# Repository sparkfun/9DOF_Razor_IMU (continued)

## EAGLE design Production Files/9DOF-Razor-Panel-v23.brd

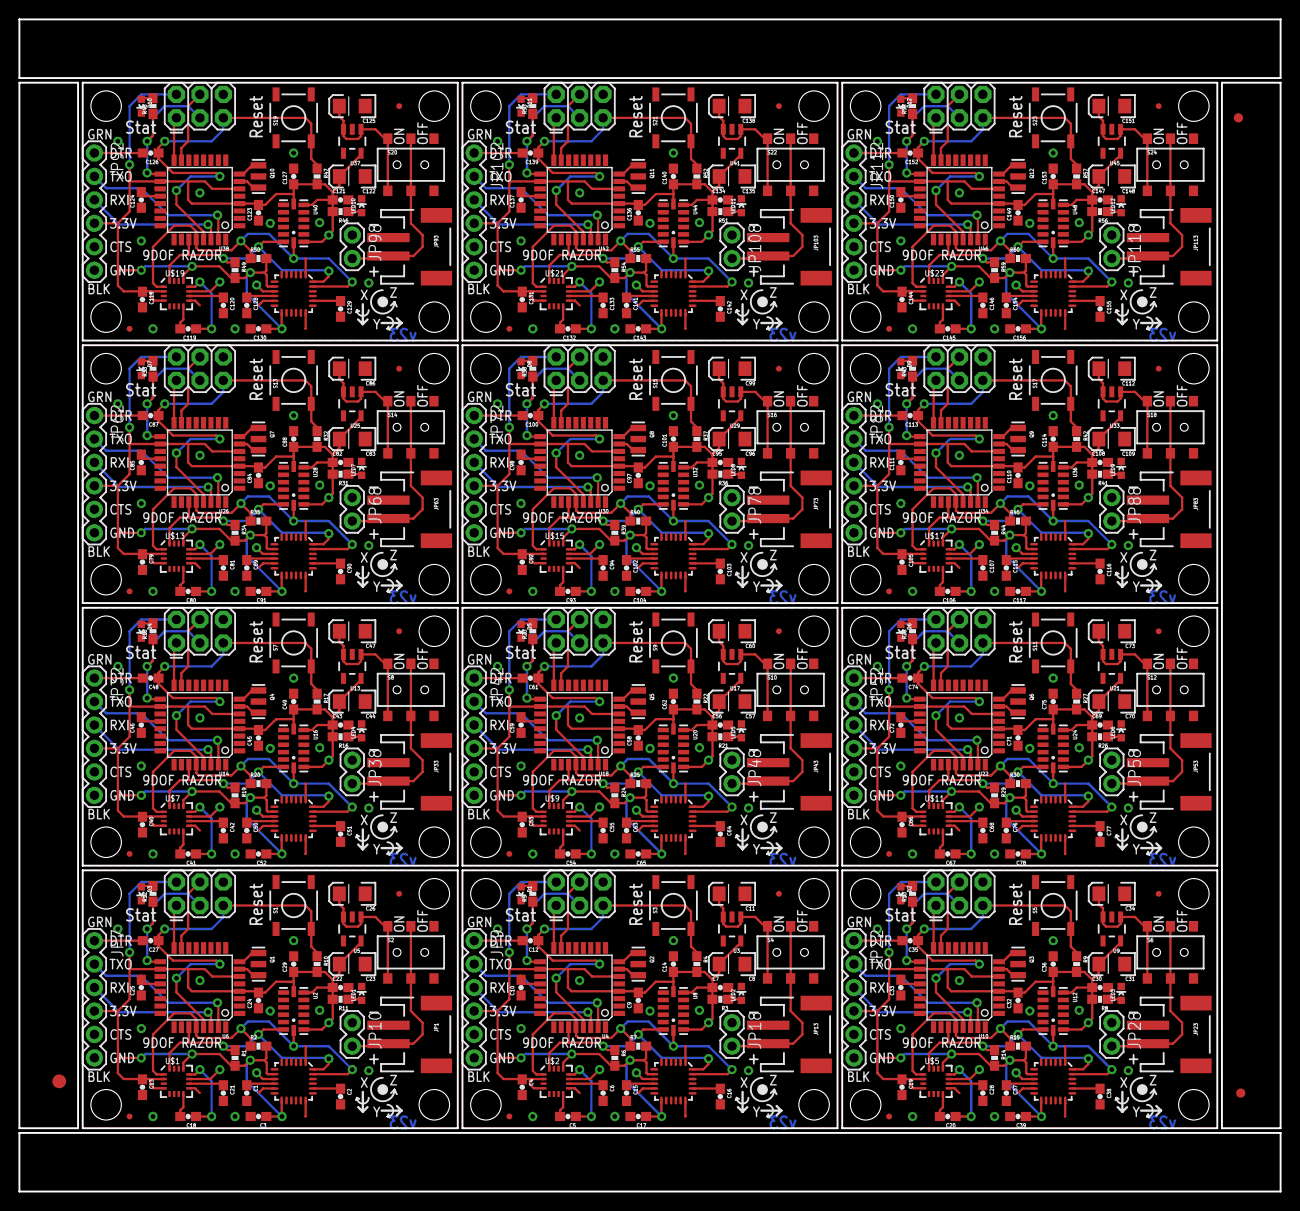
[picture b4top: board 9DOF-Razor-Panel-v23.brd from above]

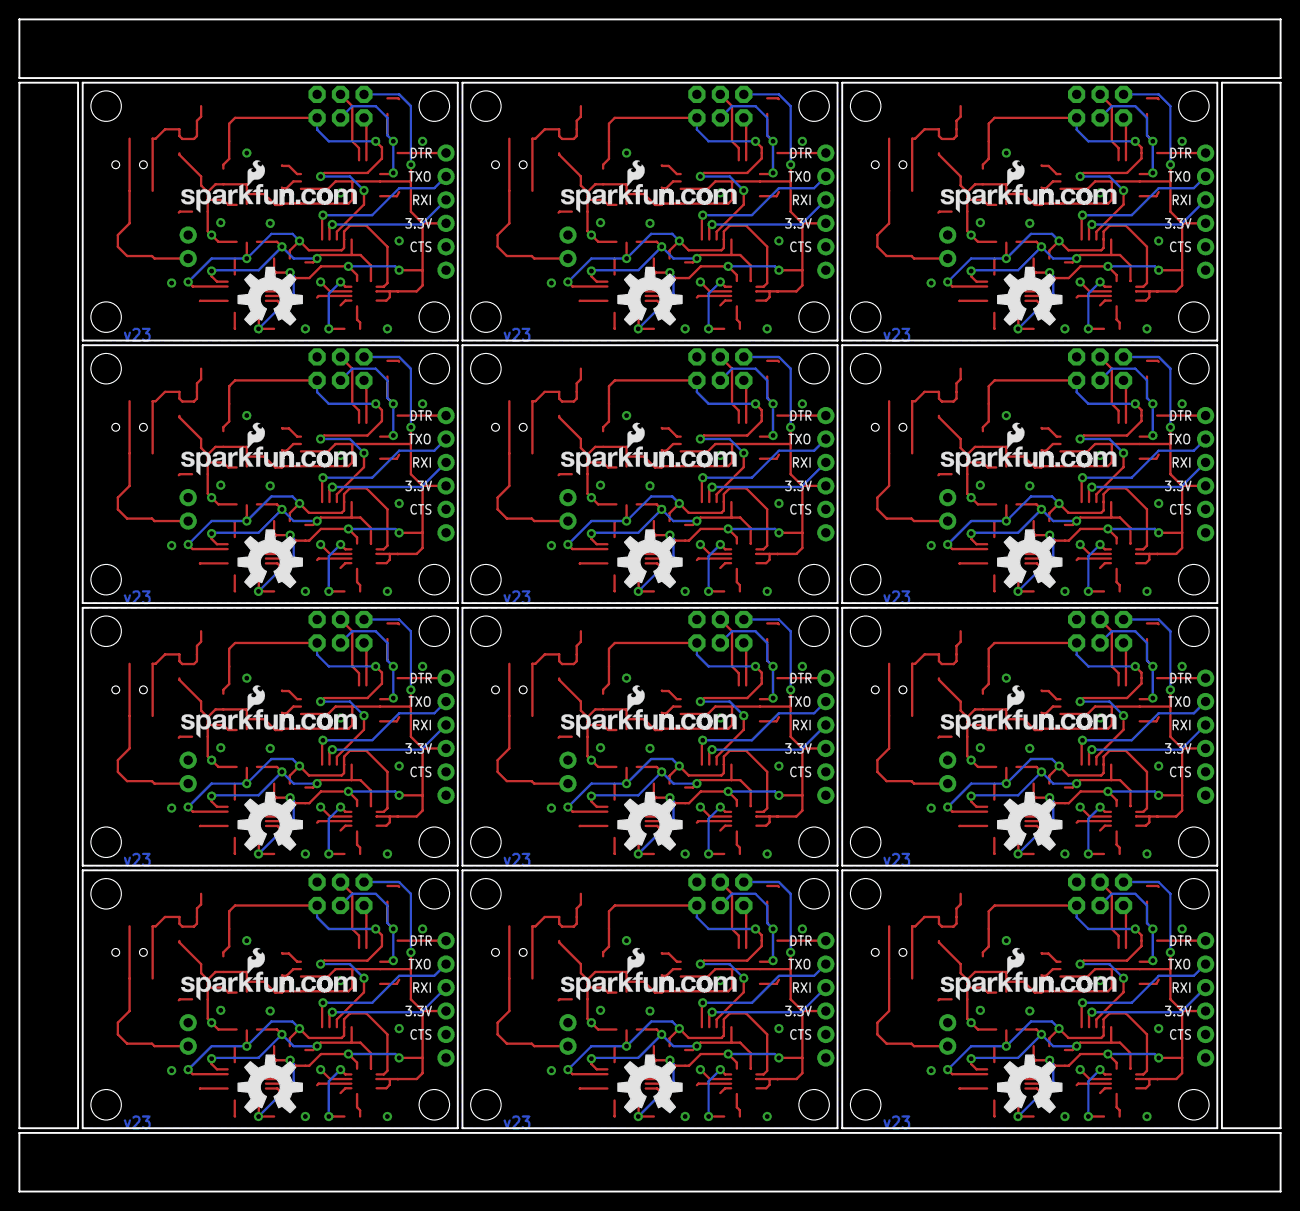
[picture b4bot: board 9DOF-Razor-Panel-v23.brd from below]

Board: 2 copper layers, 136.7 x 127.0 mm, 483 parts (24 on the bottom side), 276 nets.

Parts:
C1, C4, C7, C9, C10, C12, C13, C14, C15, C19, C22, C24, C25, C27, C29, C30, C32, C33, C35, C36, C37, C40, C43, C45, C46, C48, C49, C50, C53, C56, C58, C59, C61, C62, C63, C66, C69, C71, C72, C74, C75, C76, C79, C82, C84, C85, C87, C88, C89, C92, C95, C97, C98, C100, C101, C102, C105, C108, C110, C111, C113, C114, C115, C118, C121, C123, C124, C126, C127, C128, C131, C134, C136, C137, C139, C140, C141, C144, C147, C149, C150, C152, C153, C154: 0.1uF; 0603-CAP
C2, C16, C38, C51, C64, C77, C90, C103, C116, C129, C142, C155: 2.2nF; 0603-CAP
C3, C17, C39, C52, C65, C78, C91, C104, C117, C130, C143, C156: 10nF; 0603-CAP
C5, C18, C20, C41, C54, C67, C80, C93, C106, C119, C132, C145: 0.22uF; 0603-CAP
C6, C21, C28, C42, C55, C68, C81, C94, C107, C120, C133, C146: 4.7uF; 0603-CAP
C8, C11, C23, C26, C31, C34, C44, C47, C57, C60, C70, C73, C83, C86, C96, C99, C109, C112, C122, C125, C135, C138, C148, C151: 10uF; EIA3216
D1, D2, D3, D4, D5, D6, D7, D8, D9, D10, D11, D12: Green; LED-0603
E$1: FIDUCIAL-1.5X3
E$4, E$5: FIDUCIAL-1X2
J1, J2, J3, J4, J5, J6, J7, J8, J9, J10, J11, J12: AVR_SPI_PRG_6PTH; 2X3
JP1, JP13, JP23, JP33, JP43, JP53, JP63, JP73, JP83, JP93, JP103, JP113: JST_Horizontal; JST-2-SMD
JP2, JP4, JP5, JP6, JP14, JP15, JP16, JP17, JP24, JP25, JP26, JP27, JP34, JP35, JP36, JP37, JP44, JP45, JP46, JP47, JP54, JP55, JP56, JP57, JP64, JP65, JP66, JP67, JP74, JP75, JP76, JP77, JP84, JP85, JP86, JP87, JP94, JP95, JP96, JP97, JP104, JP105, JP106, JP107, JP114, JP115, JP116, JP117: STAND-OFF
JP3, JP8, JP21, JP31, JP41, JP51, JP61, JP71, JP81, JP91, JP101, JP111: LOGO-SFENEW; SFE-NEW-WEBLOGO
JP7, JP9, JP22, JP32, JP42, JP52, JP62, JP72, JP82, JP92, JP102, JP112: FTDI Basic; 1X06
JP10, JP18, JP28, JP38, JP48, JP58, JP68, JP78, JP88, JP98, JP108, JP118: JST_Horizontal; 1X02
JP11, JP12, JP19, JP20, JP29, JP30, JP39, JP40, JP49, JP50, JP59, JP60, JP69, JP70, JP79, JP80, JP89, JP90, JP99, JP100, JP109, JP110, JP119, JP120: FIDUCIAL1X2.5; FIDUCIAL-1X2.5
LED1, LED2, LED3, LED4, LED5, LED6, LED7, LED8, LED9, LED10, LED11, LED12: Red; LED-0603
Q1, Q2, Q3, Q4, Q5, Q6, Q7, Q8, Q9, Q10, Q11, Q12: 8MHz; RESONATOR-SMD
R1, R6, R14, R19, R24, R29, R34, R39, R44, R49, R54, R59: 4.7k; 0603-RES
R2, R7, R15, R20, R25, R30, R35, R40, R45, R50, R55, R60: 4.7K; 0603-RES
R3, R4, R8, R9, R10, R11, R16, R17, R21, R22, R26, R27, R31, R32, R36, R37, R41, R42, R46, R47, R51, R52, R56, R57: 10K; 0603-RES
R5, R12, R13, R18, R23, R28, R33, R38, R43, R48, R53, R58: 330; 0603-RES
S1, S3, S5, S7, S9, S11, S13, S15, S17, S19, S21, S23: Reset; TACTILE_SWITCH_SMD
S2, S4, S6, S8, S10, S12, S14, S16, S18, S20, S22, S24: Power; AYZ0202
U1, U7, U11, U15, U19, U23, U27, U31, U35, U39, U43, U47: ITG-32001:1; QFN-24_ITG3200_1:1
U2, U8, U12, U16, U20, U24, U28, U32, U36, U40, U44, U48: ADXL3451:1; LGA14
U3, U5, U9, U13, U17, U21, U25, U29, U33, U37, U41, U45: 3.3V; SOT23-5
U4, U6, U10, U14, U18, U22, U26, U30, U34, U38, U42, U46: ATMEGA328; TQFP32-08
U$1, U$2, U$5, U$7, U$9, U$11, U$13, U$15, U$17, U$19, U$21, U$23: HMC5883LSMD; 16LPCC
U$3, U$4, U$6, U$8, U$10, U$12, U$14, U$16, U$18, U$20, U$22, U$24: OSHW-LOGOL; OSHW-LOGO-L

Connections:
3.3V: C3.1, C13.1, C22.1, C23.A, C24.2, C29.1, J1.2, JP7.4, R1.2, R2.2, R10.2, R11.2, U1.8, U1.13, U2.1, U2.6, U2.7, U5.5, U6.4, U6.6, U6.18, U$1.2, U$1.4, U$1.13
3.3V1: C4.1, C7.1, C8.A, C9.2, C14.1, C17.1, J2.2, JP9.4, R3.2, R4.2, R6.2, R7.2, U3.5, U4.4, U4.6, U4.18, U7.8, U7.13, U8.1, U8.6, U8.7, U$2.2, U$2.4, U$2.13
3.3V2: C19.1, C30.1, C31.A, C32.2, C36.1, C39.1, J3.2, JP22.4, R8.2, R9.2, R14.2, R15.2, U9.5, U10.4, U10.6, U10.18, U11.8, U11.13, U12.1, U12.6, U12.7, U$5.2, U$5.4, U$5.13
3.3V3: C40.1, C43.1, C44.A, C45.2, C49.1, C52.1, J4.2, JP32.4, R16.2, R17.2, R19.2, R20.2, U13.5, U14.4, U14.6, U14.18, U15.8, U15.13, U16.1, U16.6, U16.7, U$7.2, U$7.4, U$7.13
3.3V4: C53.1, C56.1, C57.A, C58.2, C62.1, C65.1, J5.2, JP42.4, R21.2, R22.2, R24.2, R25.2, U17.5, U18.4, U18.6, U18.18, U19.8, U19.13, U20.1, U20.6, U20.7, U$9.2, U$9.4, U$9.13
3.3V5: C66.1, C69.1, C70.A, C71.2, C75.1, C78.1, J6.2, JP52.4, R26.2, R27.2, R29.2, R30.2, U21.5, U22.4, U22.6, U22.18, U23.8, U23.13, U24.1, U24.6, U24.7, U$11.2, U$11.4, U$11.13
3.3V6: C79.1, C82.1, C83.A, C84.2, C88.1, C91.1, J7.2, JP62.4, R31.2, R32.2, R34.2, R35.2, U25.5, U26.4, U26.6, U26.18, U27.8, U27.13, U28.1, U28.6, U28.7, U$13.2, U$13.4, U$13.13
3.3V7: C92.1, C95.1, C96.A, C97.2, C101.1, C104.1, J8.2, JP72.4, R36.2, R37.2, R39.2, R40.2, U29.5, U30.4, U30.6, U30.18, U31.8, U31.13, U32.1, U32.6, U32.7, U$15.2, U$15.4, U$15.13
3.3V8: C105.1, C108.1, C109.A, C110.2, C114.1, C117.1, J9.2, JP82.4, R41.2, R42.2, R44.2, R45.2, U33.5, U34.4, U34.6, U34.18, U35.8, U35.13, U36.1, U36.6, U36.7, U$17.2, U$17.4, U$17.13
3.3V9: C118.1, C121.1, C122.A, C123.2, C127.1, C130.1, J10.2, JP92.4, R46.2, R47.2, R49.2, R50.2, U37.5, U38.4, U38.6, U38.18, U39.8, U39.13, U40.1, U40.6, U40.7, U$19.2, U$19.4, U$19.13
3.3V10: C131.1, C134.1, C135.A, C136.2, C140.1, C143.1, J11.2, JP102.4, R51.2, R52.2, R54.2, R55.2, U41.5, U42.4, U42.6, U42.18, U43.8, U43.13, U44.1, U44.6, U44.7, U$21.2, U$21.4, U$21.13
3.3V11: C144.1, C147.1, C148.A, C149.2, C153.1, C156.1, J12.2, JP112.4, R56.2, R57.2, R59.2, R60.2, U45.5, U46.4, U46.6, U46.18, U47.8, U47.13, U48.1, U48.6, U48.7, U$23.2, U$23.4, U$23.13
AREF: C25.2, U6.20
AREF1: C10.2, U4.20
AREF2: C33.2, U10.20
AREF3: C46.2, U14.20
AREF4: C59.2, U18.20
AREF5: C72.2, U22.20
AREF6: C85.2, U26.20
AREF7: C98.2, U30.20
AREF8: C111.2, U34.20
AREF9: C124.2, U38.20
AREF10: C137.2, U42.20
AREF11: C150.2, U46.20
DTR: C27.2, JP7.1
DTR1: C12.2, JP9.1
DTR2: C35.2, JP22.1
DTR3: C48.2, JP32.1
DTR4: C61.2, JP42.1
DTR5: C74.2, JP52.1
DTR6: C87.2, JP62.1
DTR7: C100.2, JP72.1
DTR8: C113.2, JP82.1
DTR9: C126.2, JP92.1
DTR10: C139.2, JP102.1
DTR11: C152.2, JP112.1
GND: C1.2, C2.2, C3.2, C13.2, C21.2, C22.2, C23.C, C24.1, C25.1, C26.C, C29.2, D3.C, J1.6, JP1.1, JP7.5, JP7.6, JP10.1, LED1.C, Q1.2, S1.1, U1.1, U1.9, U1.11, U1.18, U2.2, U2.4, U2.5, U2.12, U5.2, U6.3, U6.5, U6.21, U$1.9, U$1.11
GND1: C4.2, C6.2, C7.2, C8.C, C9.1, C10.1, C11.C, C14.2, C15.2, C16.2, C17.2, D1.C, J2.6, JP9.5, JP9.6, JP13.1, JP18.1, LED2.C, Q2.2, S3.1, U3.2, U4.3, U4.5, U4.21, U7.1, U7.9, U7.11, U7.18, U8.2, U8.4, U8.5, U8.12, U$2.9, U$2.11
GND2: C19.2, C28.2, C30.2, C31.C, C32.1, C33.1, C34.C, C36.2, C37.2, C38.2, C39.2, D2.C, J3.6, JP22.5, JP22.6, JP23.1, JP28.1, LED3.C, Q3.2, S5.1, U9.2, U10.3, U10.5, U10.21, U11.1, U11.9, U11.11, U11.18, U12.2, U12.4, U12.5, U12.12, U$5.9, U$5.11
GND3: C40.2, C42.2, C43.2, C44.C, C45.1, C46.1, C47.C, C49.2, C50.2, C51.2, C52.2, D4.C, J4.6, JP32.5, JP32.6, JP33.1, JP38.1, LED4.C, Q4.2, S7.1, U13.2, U14.3, U14.5, U14.21, U15.1, U15.9, U15.11, U15.18, U16.2, U16.4, U16.5, U16.12, U$7.9, U$7.11
GND4: C53.2, C55.2, C56.2, C57.C, C58.1, C59.1, C60.C, C62.2, C63.2, C64.2, C65.2, D5.C, J5.6, JP42.5, JP42.6, JP43.1, JP48.1, LED5.C, Q5.2, S9.1, U17.2, U18.3, U18.5, U18.21, U19.1, U19.9, U19.11, U19.18, U20.2, U20.4, U20.5, U20.12, U$9.9, U$9.11
GND5: C66.2, C68.2, C69.2, C70.C, C71.1, C72.1, C73.C, C75.2, C76.2, C77.2, C78.2, D6.C, J6.6, JP52.5, JP52.6, JP53.1, JP58.1, LED6.C, Q6.2, S11.1, U21.2, U22.3, U22.5, U22.21, U23.1, U23.9, U23.11, U23.18, U24.2, U24.4, U24.5, U24.12, U$11.9, U$11.11
GND6: C79.2, C81.2, C82.2, C83.C, C84.1, C85.1, C86.C, C88.2, C89.2, C90.2, C91.2, D7.C, J7.6, JP62.5, JP62.6, JP63.1, JP68.1, LED7.C, Q7.2, S13.1, U25.2, U26.3, U26.5, U26.21, U27.1, U27.9, U27.11, U27.18, U28.2, U28.4, U28.5, U28.12, U$13.9, U$13.11
GND7: C92.2, C94.2, C95.2, C96.C, C97.1, C98.1, C99.C, C101.2, C102.2, C103.2, C104.2, D8.C, J8.6, JP72.5, JP72.6, JP73.1, JP78.1, LED8.C, Q8.2, S15.1, U29.2, U30.3, U30.5, U30.21, U31.1, U31.9, U31.11, U31.18, U32.2, U32.4, U32.5, U32.12, U$15.9, U$15.11
GND8: C105.2, C107.2, C108.2, C109.C, C110.1, C111.1, C112.C, C114.2, C115.2, C116.2, C117.2, D9.C, J9.6, JP82.5, JP82.6, JP83.1, JP88.1, LED9.C, Q9.2, S17.1, U33.2, U34.3, U34.5, U34.21, U35.1, U35.9, U35.11, U35.18, U36.2, U36.4, U36.5, U36.12, U$17.9, U$17.11
GND9: C118.2, C120.2, C121.2, C122.C, C123.1, C124.1, C125.C, C127.2, C128.2, C129.2, C130.2, D10.C, J10.6, JP92.5, JP92.6, JP93.1, JP98.1, LED10.C, Q10.2, S19.1, U37.2, U38.3, U38.5, U38.21, U39.1, U39.9, U39.11, U39.18, U40.2, U40.4, U40.5, U40.12, U$19.9, U$19.11
GND10: C131.2, C133.2, C134.2, C135.C, C136.1, C137.1, C138.C, C140.2, C141.2, C142.2, C143.2, D11.C, J11.6, JP102.5, JP102.6, JP103.1, JP108.1, LED11.C, Q11.2, S21.1, U41.2, U42.3, U42.5, U42.21, U43.1, U43.9, U43.11, U43.18, U44.2, U44.4, U44.5, U44.12, U$21.9, U$21.11
GND11: C144.2, C146.2, C147.2, C148.C, C149.1, C150.1, C151.C, C153.2, C154.2, C155.2, C156.2, D12.C, J12.6, JP112.5, JP112.6, JP113.1, JP118.1, LED12.C, Q12.2, S23.1, U45.2, U46.3, U46.5, U46.21, U47.1, U47.9, U47.11, U47.18, U48.2, U48.4, U48.5, U48.12, U$23.9, U$23.11
MISO: J1.1, U6.16
MISO1: J2.1, U4.16
MISO2: J3.1, U10.16
MISO3: J4.1, U14.16
MISO4: J5.1, U18.16
MISO5: J6.1, U22.16
MISO6: J7.1, U26.16
MISO7: J8.1, U30.16
MISO8: J9.1, U34.16
MISO9: J10.1, U38.16
MISO10: J11.1, U42.16
MISO11: J12.1, U46.16
MOSI: J1.4, U6.15
MOSI1: J2.4, U4.15
MOSI2: J3.4, U10.15
MOSI3: J4.4, U14.15
MOSI4: J5.4, U18.15
MOSI5: J6.4, U22.15
MOSI6: J7.4, U26.15
MOSI7: J8.4, U30.15
MOSI8: J9.4, U34.15
MOSI9: J10.4, U38.15
MOSI10: J11.4, U42.15
MOSI11: J12.4, U46.15
unnamed: C18.2, U$1.8
unnamed: C18.1, U$1.12
unnamed: C1.1, U1.10
unnamed: C2.1, U1.20
unnamed: LED2.A, R3.1
unnamed: C21.1, U$1.10
unnamed: D1.A, R5.2
unnamed: Q2.1, U4.8
unnamed: Q2.3, U4.7
unnamed: JP13.2, JP18.2, S4.2, S4.5
unnamed: C15.1, U7.10
unnamed: D3.A, R12.2
unnamed: Q1.1, U6.8
unnamed: Q1.3, U6.7
unnamed: JP1.2, JP10.2, S2.2, S2.5
unnamed: C16.1, U7.20
unnamed: C5.2, U$2.8
unnamed: C5.1, U$2.12
unnamed: C6.1, U$2.10
unnamed: LED3.A, R8.1
unnamed: D2.A, R13.2
unnamed: Q3.1, U10.8
unnamed: Q3.3, U10.7
unnamed: JP23.2, JP28.2, S6.2, S6.5
unnamed: C37.1, U11.10
unnamed: C38.1, U11.20
unnamed: C20.2, U$5.8
unnamed: C20.1, U$5.12
unnamed: C28.1, U$5.10
unnamed: LED4.A, R16.1
unnamed: D4.A, R18.2
unnamed: Q4.1, U14.8
unnamed: Q4.3, U14.7
unnamed: JP33.2, JP38.2, S8.2, S8.5
unnamed: C50.1, U15.10
unnamed: C51.1, U15.20
unnamed: C41.2, U$7.8
unnamed: LED1.A, R11.1
unnamed: C41.1, U$7.12
unnamed: C42.1, U$7.10
unnamed: LED5.A, R21.1
unnamed: D5.A, R23.2
unnamed: Q5.1, U18.8
unnamed: Q5.3, U18.7
unnamed: JP43.2, JP48.2, S10.2, S10.5
unnamed: C63.1, U19.10
unnamed: C64.1, U19.20
unnamed: C54.2, U$9.8
unnamed: C54.1, U$9.12
unnamed: C55.1, U$9.10
unnamed: LED6.A, R26.1
unnamed: D6.A, R28.2
unnamed: Q6.1, U22.8
unnamed: Q6.3, U22.7
unnamed: JP53.2, JP58.2, S12.2, S12.5
unnamed: C76.1, U23.10
unnamed: C77.1, U23.20
unnamed: C67.2, U$11.8
unnamed: C67.1, U$11.12
unnamed: C68.1, U$11.10
unnamed: LED7.A, R31.1
unnamed: D7.A, R33.2
unnamed: Q7.1, U26.8
unnamed: Q7.3, U26.7
unnamed: JP63.2, JP68.2, S14.2, S14.5
unnamed: C89.1, U27.10
unnamed: C90.1, U27.20
unnamed: C80.2, U$13.8
unnamed: C80.1, U$13.12
unnamed: C81.1, U$13.10
unnamed: LED8.A, R36.1
unnamed: D8.A, R38.2
unnamed: Q8.1, U30.8
unnamed: Q8.3, U30.7
unnamed: JP73.2, JP78.2, S16.2, S16.5
unnamed: C102.1, U31.10
unnamed: C103.1, U31.20
unnamed: C93.2, U$15.8
unnamed: C93.1, U$15.12
unnamed: C94.1, U$15.10
unnamed: LED9.A, R41.1
unnamed: D9.A, R43.2
unnamed: Q9.1, U34.8
unnamed: Q9.3, U34.7
unnamed: JP83.2, JP88.2, S18.2, S18.5
unnamed: C115.1, U35.10
unnamed: C116.1, U35.20
unnamed: C106.2, U$17.8
unnamed: C106.1, U$17.12
unnamed: C107.1, U$17.10
unnamed: LED10.A, R46.1
unnamed: D10.A, R48.2
unnamed: Q10.1, U38.8
unnamed: Q10.3, U38.7
unnamed: JP93.2, JP98.2, S20.2, S20.5
unnamed: C128.1, U39.10
unnamed: C129.1, U39.20
unnamed: C119.2, U$19.8
unnamed: C119.1, U$19.12
unnamed: C120.1, U$19.10
unnamed: LED11.A, R51.1
unnamed: D11.A, R53.2
unnamed: Q11.1, U42.8
unnamed: Q11.3, U42.7
unnamed: JP103.2, JP108.2, S22.2, S22.5
unnamed: C141.1, U43.10
unnamed: C142.1, U43.20
unnamed: C132.2, U$21.8
unnamed: C132.1, U$21.12
unnamed: C133.1, U$21.10
unnamed: LED12.A, R56.1
unnamed: D12.A, R58.2
unnamed: Q12.1, U46.8
unnamed: Q12.3, U46.7
unnamed: JP113.2, JP118.2, S24.2, S24.5
unnamed: C154.1, U47.10
unnamed: C155.1, U47.20
unnamed: C145.2, U$23.8
unnamed: C145.1, U$23.12
unnamed: C146.1, U$23.10
RAW: C26.A, S2.1, S2.4, U5.1, U5.3
RAW1: C11.A, S4.1, S4.4, U3.1, U3.3
RAW2: C34.A, S6.1, S6.4, U9.1, U9.3
RAW3: C47.A, S8.1, S8.4, U13.1, U13.3
RAW4: C60.A, S10.1, S10.4, U17.1, U17.3
RAW5: C73.A, S12.1, S12.4, U21.1, U21.3
RAW6: C86.A, S14.1, S14.4, U25.1, U25.3
RAW7: C99.A, S16.1, S16.4, U29.1, U29.3
RAW8: C112.A, S18.1, S18.4, U33.1, U33.3
RAW9: C125.A, S20.1, S20.4, U37.1, U37.3
RAW10: C138.A, S22.1, S22.4, U41.1, U41.3
RAW11: C151.A, S24.1, S24.4, U45.1, U45.3
RESET: C27.1, J1.5, R10.1, S1.3, U6.29
RESET1: C12.1, J2.5, R4.1, S3.3, U4.29
RESET2: C35.1, J3.5, R9.1, S5.3, U10.29
RESET3: C48.1, J4.5, R17.1, S7.3, U14.29
RESET4: C61.1, J5.5, R22.1, S9.3, U18.29
RESET5: C74.1, J6.5, R27.1, S11.3, U22.29
RESET6: C87.1, J7.5, R32.1, S13.3, U26.29
RESET7: C100.1, J8.5, R37.1, S15.3, U30.29
RESET8: C113.1, J9.5, R42.1, S17.3, U34.29
RESET9: C126.1, J10.5, R47.1, S19.3, U38.29
RESET10: C139.1, J11.5, R52.1, S21.3, U42.29
RESET11: C152.1, J12.5, R57.1, S23.3, U46.29
RXI: JP7.3, U6.30
RXI1: JP9.3, U4.30
RXI2: JP22.3, U10.30
RXI3: JP32.3, U14.30
RXI4: JP42.3, U18.30
RXI5: JP52.3, U22.30
RXI6: JP62.3, U26.30
RXI7: JP72.3, U30.30
RXI8: JP82.3, U34.30
RXI9: JP92.3, U38.30
RXI10: JP102.3, U42.30
RXI11: JP112.3, U46.30
SCK: J1.3, R12.1, U6.17
SCK1: J2.3, R5.1, U4.17
SCK2: J3.3, R13.1, U10.17
SCK3: J4.3, R18.1, U14.17
SCK4: J5.3, R23.1, U18.17
SCK5: J6.3, R28.1, U22.17
SCK6: J7.3, R33.1, U26.17
SCK7: J8.3, R38.1, U30.17
SCK8: J9.3, R43.1, U34.17
SCK9: J10.3, R48.1, U38.17
SCK10: J11.3, R53.1, U42.17
SCK11: J12.3, R58.1, U46.17
SCL: R2.1, U1.23, U2.14, U6.28, U$1.1
SCL1: R7.1, U4.28, U7.23, U8.14, U$2.1
SCL2: R15.1, U10.28, U11.23, U12.14, U$5.1
SCL3: R20.1, U14.28, U15.23, U16.14, U$7.1
SCL4: R25.1, U18.28, U19.23, U20.14, U$9.1
SCL5: R30.1, U22.28, U23.23, U24.14, U$11.1
SCL6: R35.1, U26.28, U27.23, U28.14, U$13.1
SCL7: R40.1, U30.28, U31.23, U32.14, U$15.1
SCL8: R45.1, U34.28, U35.23, U36.14, U$17.1
SCL9: R50.1, U38.28, U39.23, U40.14, U$19.1
SCL10: R55.1, U42.28, U43.23, U44.14, U$21.1
SCL11: R60.1, U46.28, U47.23, U48.14, U$23.1
SDA: R1.1, U1.24, U2.13, U6.27, U$1.16
SDA1: R6.1, U4.27, U7.24, U8.13, U$2.16
SDA2: R14.1, U10.27, U11.24, U12.13, U$5.16
SDA3: R19.1, U14.27, U15.24, U16.13, U$7.16
SDA4: R24.1, U18.27, U19.24, U20.13, U$9.16
SDA5: R29.1, U22.27, U23.24, U24.13, U$11.16
SDA6: R34.1, U26.27, U27.24, U28.13, U$13.16
SDA7: R39.1, U30.27, U31.24, U32.13, U$15.16
SDA8: R44.1, U34.27, U35.24, U36.13, U$17.16
SDA9: R49.1, U38.27, U39.24, U40.13, U$19.16
SDA10: R54.1, U42.27, U43.24, U44.13, U$21.16
SDA11: R59.1, U46.27, U47.24, U48.13, U$23.16
TXO: JP7.2, U6.31
TXO1: JP9.2, U4.31
TXO2: JP22.2, U10.31
TXO3: JP32.2, U14.31
TXO4: JP42.2, U18.31
TXO5: JP52.2, U22.31
TXO6: JP62.2, U26.31
TXO7: JP72.2, U30.31
TXO8: JP82.2, U34.31
TXO9: JP92.2, U38.31
TXO10: JP102.2, U42.31
TXO11: JP112.2, U46.31

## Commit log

2013-08-09 Initial commit of software and hardware files
    Commit includes:
    - V23 hardware files
    - Bootloader hex file
    - Test firmware hex file
    - Combined Hex file used in Production
    v23 Hardware changes:
2013-08-09 Updated ReadMe
    Edited Read Me to accurately reflect description on the website.
2013-08-14 General cleanup in schematic
    Added:
    - Rev code on PCB
    - Minor trace cleanup on mag IC
    Replaced:
    - Net labels with flag style markers
    - Old Frame design with new Frame design that includes CC3.0 and OSHW
2013-08-14 Changed all Y junctions to T junctions
    On PCB: all traces with Y junctions are now T junctions.
2013-09-17 Created Panel
    Normal sized panel with rails
2014-01-21 Updated product firmware
    Adding updated firmware files, including previous revision history found
    in ~OLD.zip folder. Also including production hex files for bootloader
    as well as a combined hex file that contains both bootloader and v23
    firmware.
2014-01-21 Updating ReadMe
    Adding the standard jazz: product description, pic links, and such.
2014-01-21 Updated firmware copyright
    New date and author info.
2014-01-21 Fixing README, adding .GITIGNORE
2014-01-21 Update README.md
    Fixing title typos.
2015-03-20 - add a 3D model of the Sparkfun 9DOF Razor (designed with Solidworks 2013) - add textures based on official images available on the product page https://www.sparkfun.com/products/10736
2016-08-01 Standardizing file names.
2016-08-01 Initial commit of v24.
2016-08-01 Schematic cleanup, bottom re-routing.
2016-08-01 Cleaning up routing.
2016-08-02 Brd/sch tweaks after engineer checklist.
2016-08-08 Reorganizing expansion header(s), layout cleanup, PROD_ID's.
2016-08-08 Adding labels to bottom side.
2016-09-12 Updating version number to redboard release - v30
2016-09-19 Post-review changes - swapping 3.3V and GND, moving switch in.
2016-09-19 Adding MPU-9250 documentation.
2016-09-19 Checklist adjustments - mostly silkscreen nudging.
2016-10-26 panel
2016-11-04 Removing old ATmega328-based firmware. Adding new bootloader.
2016-11-04 Removing old firmware.
2016-11-04 Cleanup bootloader directory.
2016-11-16 Adding bootload pin support to bootloader.
2016-11-22 Initial commit of 9DoF Razor IMU M0 example firmware.
2016-11-22 Updating default and max frequency to 100Hz
2016-11-28 Adding #ifdef catch to make FlashStorage library optional.
2016-11-28 Fixing return value from initSD
2016-11-29 Adding production test code.
2016-11-29 Adding license, updating readme.
2016-12-01 Squashed 'Libraries/Arduino/' content from commit 3370a18
    git-subtree-dir: Libraries/Arduino
    git-subtree-split: 3370a188e7f8007900c323672a89cbfaf47e1299
2016-12-12 Value Added to .brd File
    Right Angle Slide Switch Added for 3D Modeling
2019-03-14 Update gyro calibration implementation
    *dmp_enable_feature* (**DMP_FEATURE_GYRO_CAL**) needs to be called in conjunction with **DMP_FEATURE_SEND_CAL_GYRO**
    See: https://github.com/sparkfun/9DOF_Razor_IMU/blob/master/Libraries/Arduino/src/util/inv_mpu_dmp_motion_driver.c#L1090
    Brought up by in this issue: https://github.com/sparkfun/9DOF_Razor_IMU/issues/10
    Tested to work.
2019-07-13 Fix euler logging comment
    The angles are actually printed in Pitch, Roll, Yaw order.
2020-03-09 Fixes eular angle calculation from quaternions
